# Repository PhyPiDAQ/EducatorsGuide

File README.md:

# PhyPiDAQ  Educators' Guide README

[Full Educators Tutorial in English](EducatorsGuide.md)

[Ausführliche Anleitung in deutscher Sprache](Anleitung.md)

## Summary  

The PhyPiDAQ project aims to provide students access to state-of-the-art measurement technology and data
acquisition tools. As it is based on standardized protocols and hardware, it can not only be cheaper to
set up than similar offers but also gives a great educational introduction in methods of modern science. 
Additionally, the measuring technology can be run off a power bank, making it portable and allowing great
experiments in nature. This project targets students from middle school up to undergraduates at the university
level with great matching educational concepts.
  
This is the general tutorial aming at educators. 
If you are looking for hardware guides, build instructions or software details, please check out our
other [repositories](https://github.com/PhyPiDAQ).

#### Currently available Documentation

 - [Software Description](https://github.com/PhyPiDAQ/PhyPiDAQ/tree/main/docs/Documentation_en.md)
 - [Educators Guide](https://github.com/PhyPiDAQ/EducatorsGuide/blob/main/EducatorsGuide.md)
 - [Hardware build instructions](https://github.com/PhyPiDAQ/MeasuringCase/blob/main/Documentation_en.md)

## Übersicht in Deutscher Sprache

Das PhyPiDAQ-Projekt zielt darauf ab, Studierenden und SchülerInnen Zugang zu modernster Messtechnik
und Datenerfassung zu geben. Da es auf offenen, standardisierten Protokollen und leicht verfügbarer
Hardware basiert, kann es nicht nur kostengünstig eingerichtet werden, sondern bietet auch eine 
hervorragende pädagogische Einführung in die Messmethoden der modernen Wissenschaft. Die Messtechnik 
kann mit einer Powerbank betrieben werden, was sie tragbar macht und Experimente auch in freier Natur
ermöglicht. *PhyPiDAQ* richtet sich an SchülerInnen von der Mittelstufe bis hin zu Studierenden auf Universitätsebene. 

Diese allgemeine Anleitung richtet sich an Lehrkräfte.
Wenn Sie nach Hardware-Beschreibungen, Bauanleitungen oder einer detaillierten Beschreibung der Software suchen, schauen Sie sich bitte unsere anderen
[Repositories](https://github.com/PhyPiDAQ) an.

#### Derzeit verfügbare Dokumentation

 - [Anleitung für Lehrkräfte](https://github.com/PhyPiDAQ/EducatorsGuide/blob/main/Anleitung.md)
 - [Einführungskurs für Schülerinnen und Schüler](https://github.com/PhyPiDAQ/EducatorsGuide/blob/main/docs/Kurs_digitale_Messwerterfassung_mit_PhyPiDAQ.pdf)
 - [Beschreibung der Software](https://github.com/PhyPiDAQ/PhyPiDAQ/blob/main/docs/Dokumentation_de.md)
 - [Bauanleitung Messkoffer](https://github.com/PhyPiDAQ/MeasuringCase/blob/main/Dokumentation_de.md)
 - [Leitfaden für das Experimentieren mit PhyPiDAQ](https://github.com/LangP14/EducatorsGuide/blob/main/Leitfaden%20fuer%20das%20Experimentieren%20mit%20PhyPiDAQ.md)

## Contributing

For information on how to contribute to this project, please refer to the [CONTRIBUTING.md](CONTRIBUTING.md) file.

## License

This project is licensed under the `MIT BSD 2-Clause License`. For more information refer to the [LICENSE](LICENSE) file.

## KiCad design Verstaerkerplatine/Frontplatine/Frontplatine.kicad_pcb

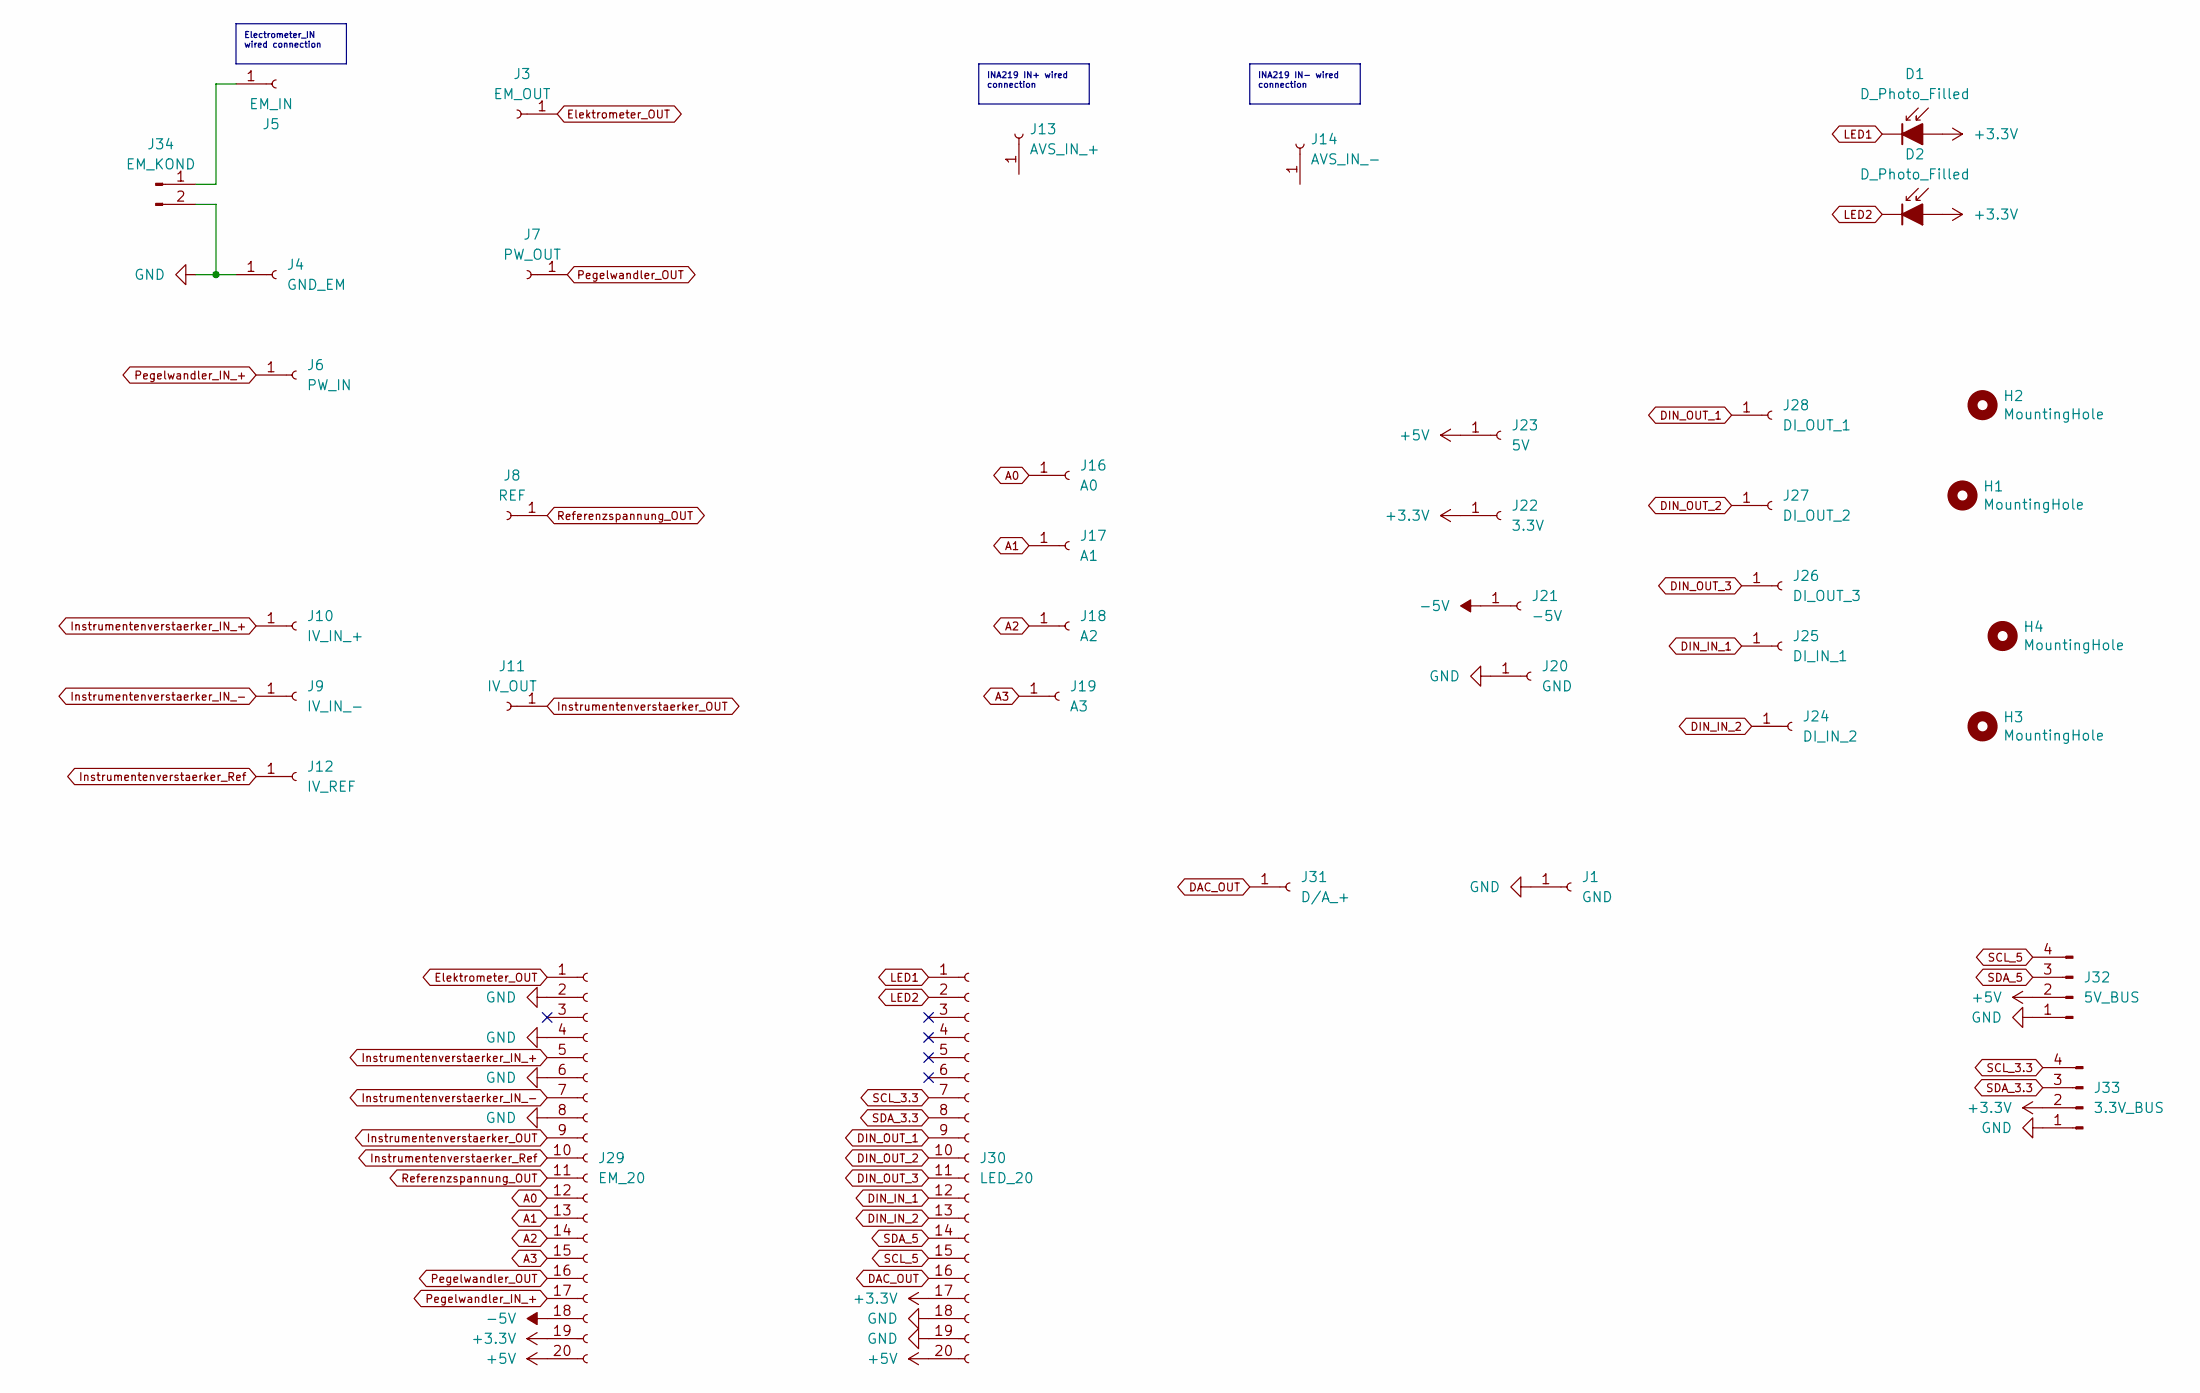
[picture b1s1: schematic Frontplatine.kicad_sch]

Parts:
D1, D2: D_Photo_Filled; LED_D5.0mm_FlatTop
H1, H2, H3, H4: MountingHole; MountingHole_3.2mm_M3
J1, J20: GND; MBU_1
J3: EM_OUT; MBU_1
J4: GND_EM; MBU_1
J5: EM_IN; MBU_1
J6: PW_IN; MBU_1
J7: PW_OUT; MBU_1
J8: REF; MBU_1
J9: IV_IN_-; MBU_1
J10: IV_IN_+; MBU_1
J11: IV_OUT; MBU_1
J12: IV_REF; MBU_1
J13: AVS_IN_+; MBU_1
J14: AVS_IN_-; MBU_1
J16: A0; MBU_1
J17: A1; MBU_1
J18: A2; MBU_1
J19: A3; MBU_1
J21: -5V; MBU_1
J22: 3.3V; MBU_1
J23: 5V; MBU_1
J24: DI_IN_2; MBU_1
J25: DI_IN_1; MBU_1
J26: DI_OUT_3; MBU_1
J27: DI_OUT_2; MBU_1
J28: DI_OUT_1; MBU_1
J29: EM_20; PinHeader_1x20_P2.54mm_Vertical_SMD_Pin1Left
J30: LED_20; PinHeader_1x20_P2.54mm_Vertical_SMD_Pin1Left
J31: D/A_+; MBU_1
J32: 5V_BUS; PinSocket_1x04_P2.00mm_Vertical
J33: 3.3V_BUS; PinSocket_1x04_P2.00mm_Vertical
J34: EM_KOND; PinSocket_1x02_P2.54mm_Vertical

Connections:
+3.3V: D1.2 (A), D2.2 (A), J22.1, J29.19, J30.17, J33.2
+5V: J23.1, J29.20, J30.20, J32.2
-5V: J21.1, J29.18
A0: J16.1, J29.12
A1: J17.1, J29.13
A2: J18.1, J29.14
A3: J19.1, J29.15
DAC_OUT: J30.16, J31.1
DIN_IN_1: J25.1, J30.12
DIN_IN_2: J24.1, J30.13
DIN_OUT_1: J28.1, J30.9
DIN_OUT_2: J27.1, J30.10
DIN_OUT_3: J26.1, J30.11
Elektrometer_OUT: J3.1, J29.1
GND: J1.1, J4.1, J20.1, J29.2, J29.4, J29.6, J29.8, J30.18, J30.19, J32.1, J33.1, J34.2
Instrumentenverstaerker_IN_+: J10.1, J29.5
Instrumentenverstaerker_IN_-: J9.1, J29.7
Instrumentenverstaerker_OUT: J11.1, J29.9
Instrumentenverstaerker_Ref: J12.1, J29.10
LED1: D1.1 (K), J30.1
LED2: D2.1 (K), J30.2
unnamed: J5.1, J34.1
Pegelwandler_IN_+: J6.1, J29.17
Pegelwandler_OUT: J7.1, J29.16
Referenzspannung_OUT: J8.1, J29.11
SCL_3.3: J30.7, J33.4
SCL_5: J30.15, J32.4
SDA_3.3: J30.8, J33.3
SDA_5: J30.14, J32.3

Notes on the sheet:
INA219 IN+ wired connection
Electrometer_IN wired connection
INA219 IN- wired connection

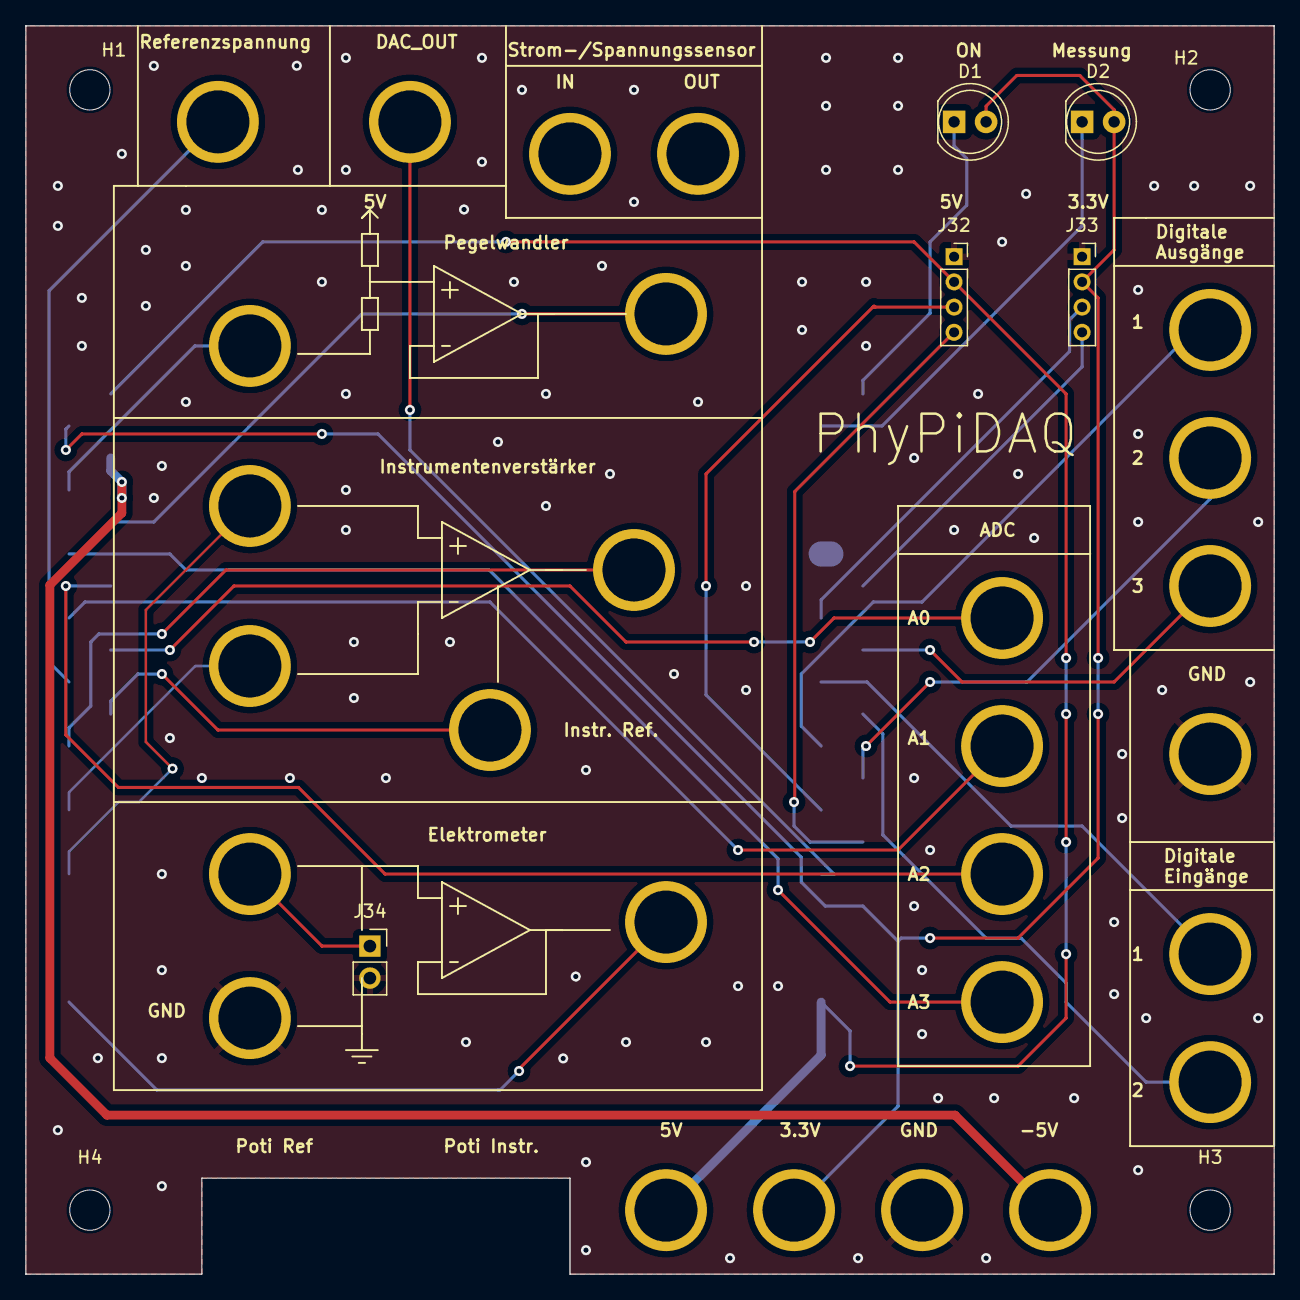
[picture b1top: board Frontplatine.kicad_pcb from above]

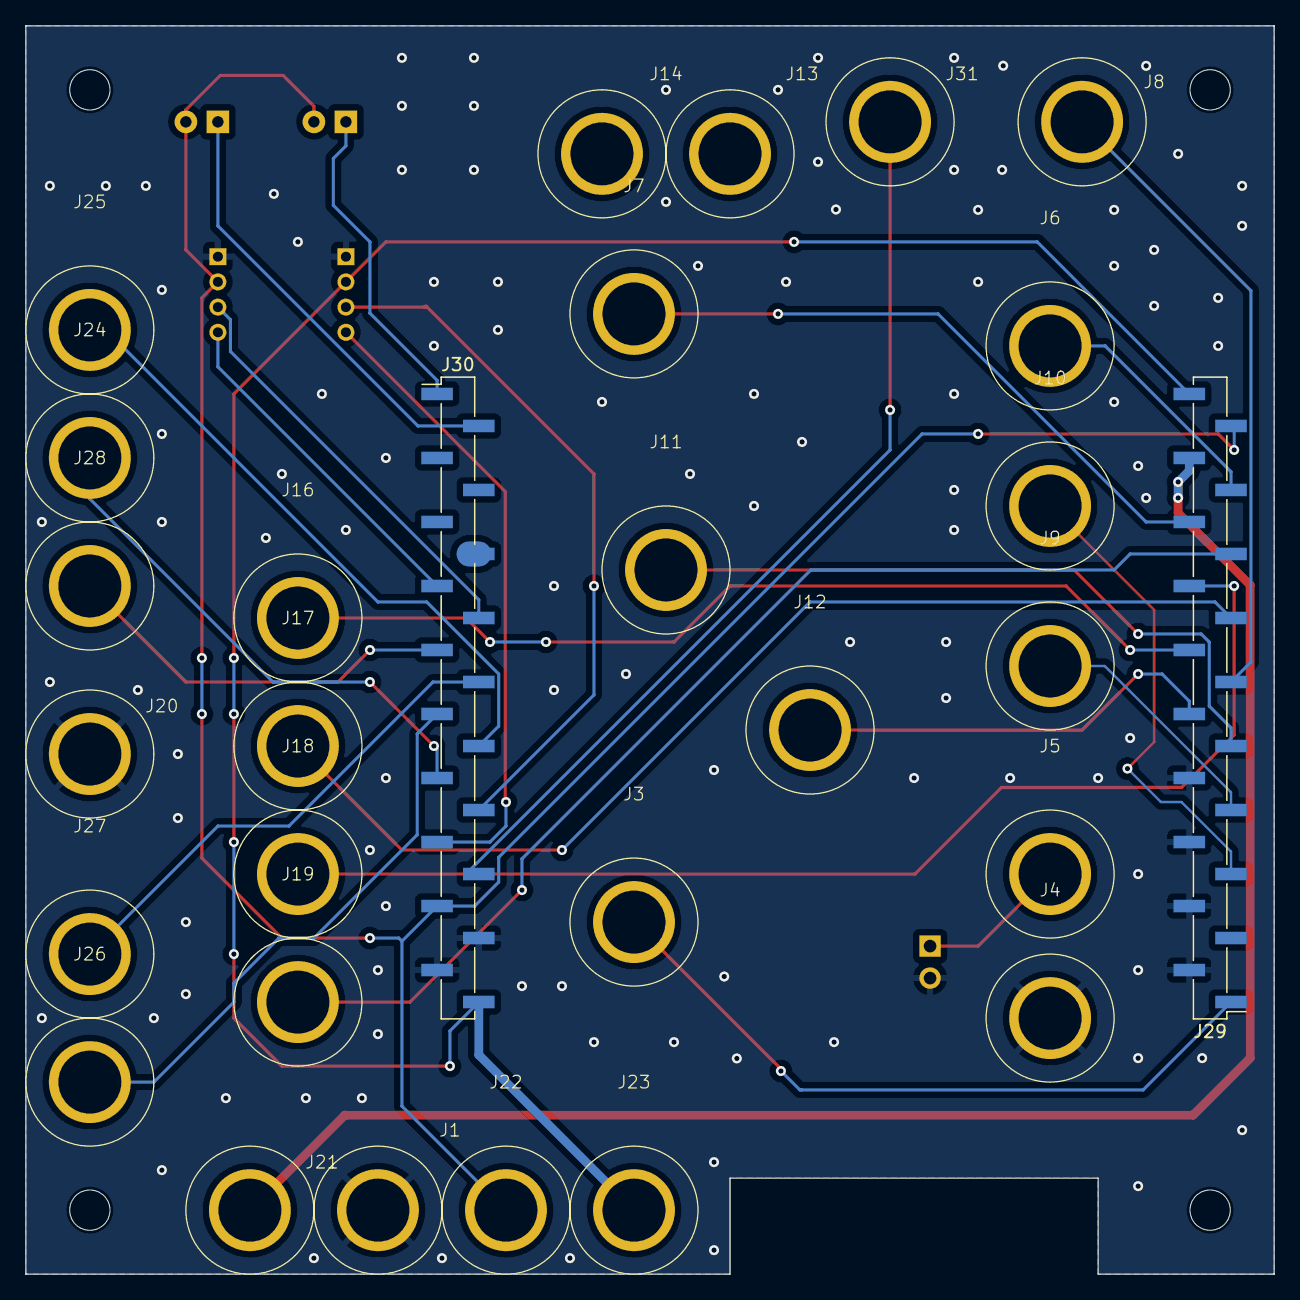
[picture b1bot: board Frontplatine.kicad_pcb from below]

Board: 2 copper layers, 99.1 x 99.1 mm, 38 parts (29 on the bottom side), 29 nets.

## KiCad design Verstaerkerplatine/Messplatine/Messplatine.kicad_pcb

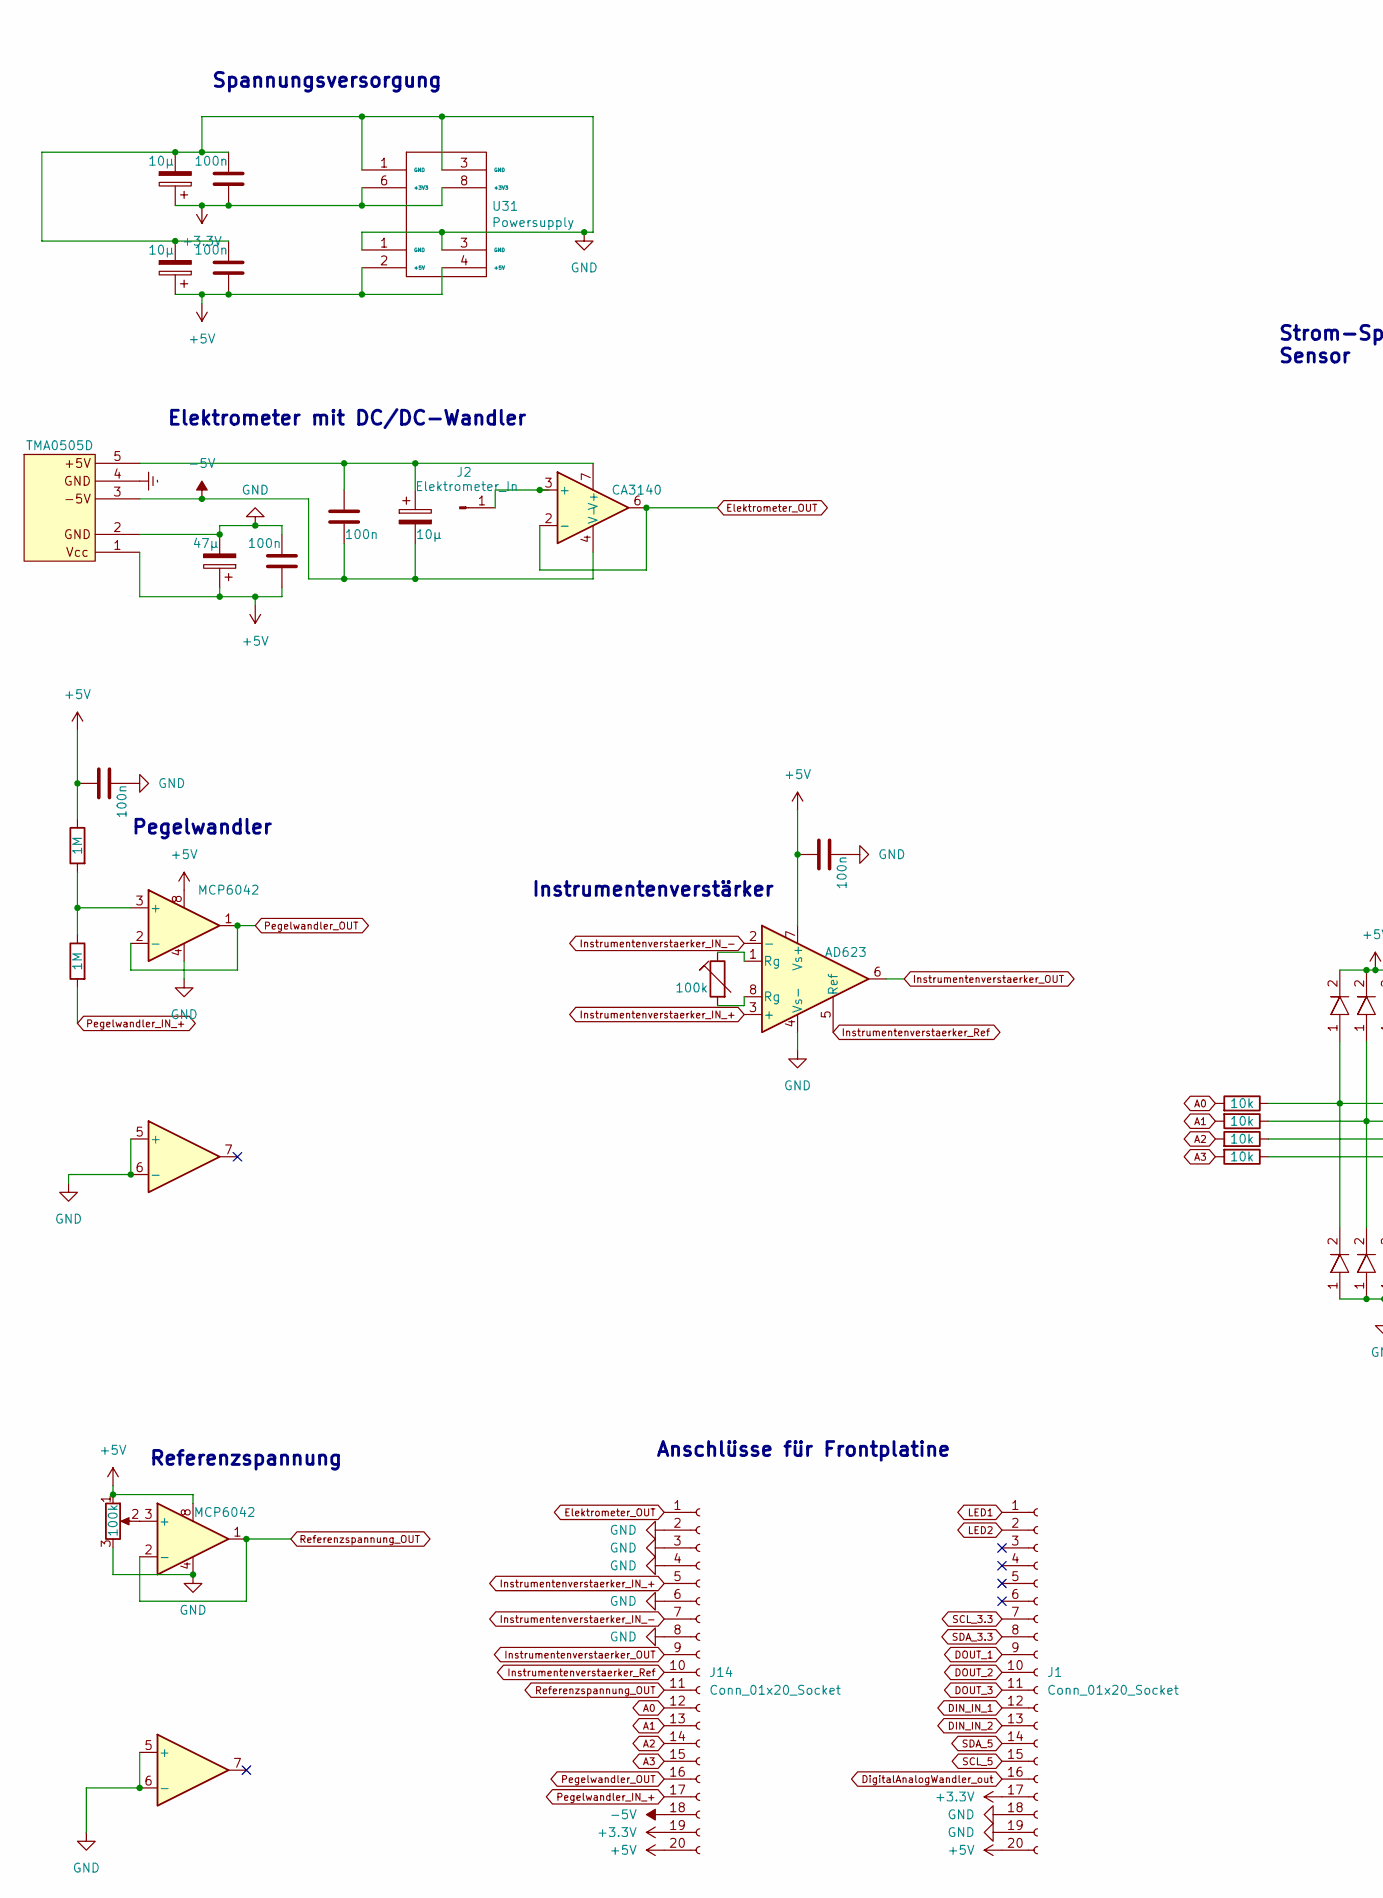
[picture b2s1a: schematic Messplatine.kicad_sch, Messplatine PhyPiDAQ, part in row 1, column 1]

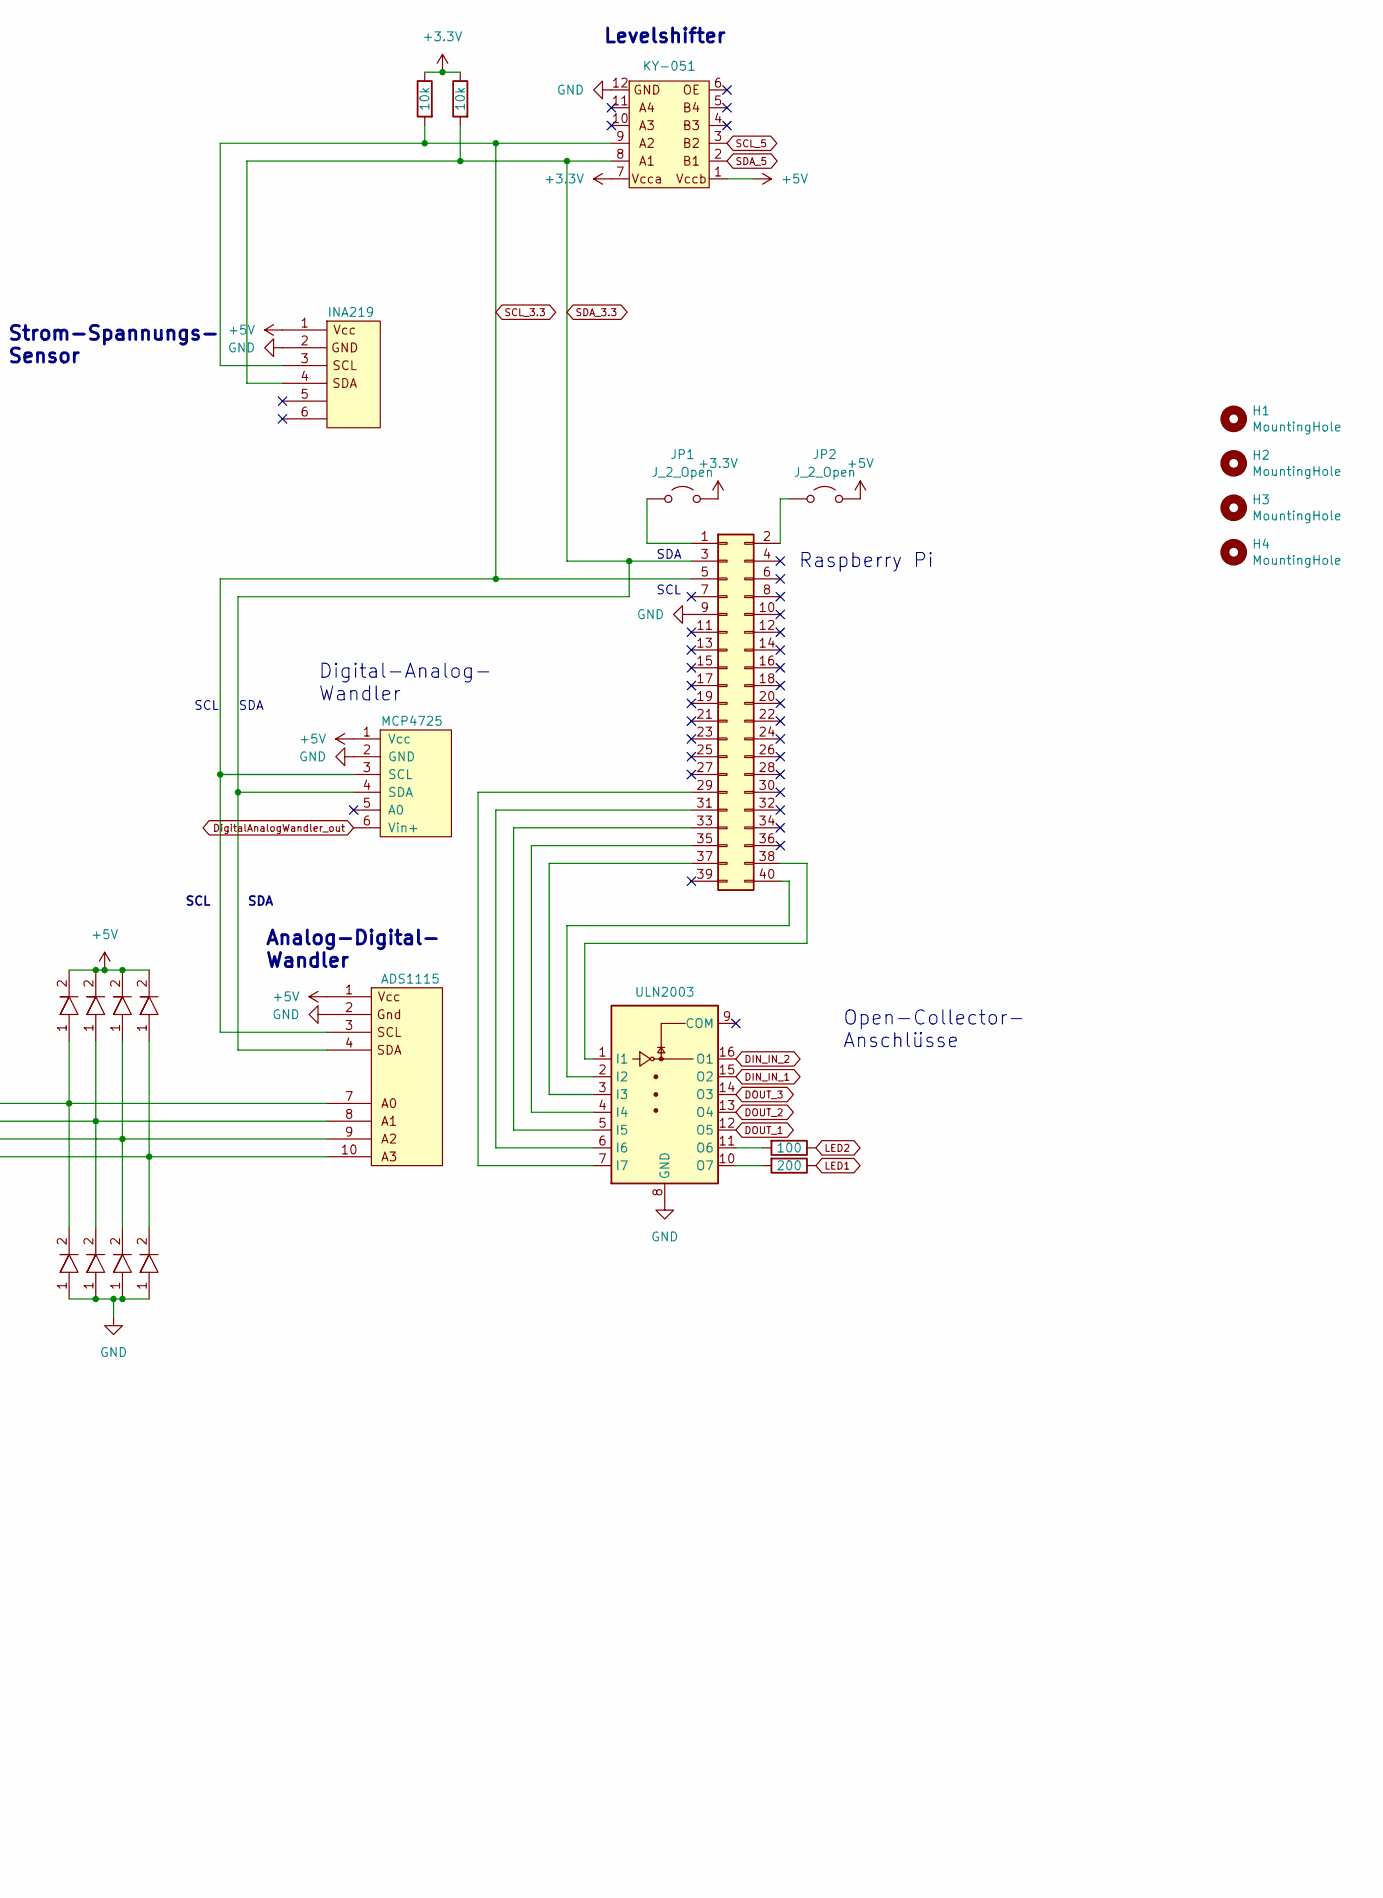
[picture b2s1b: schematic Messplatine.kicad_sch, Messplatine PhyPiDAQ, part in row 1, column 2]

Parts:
C1, C2, C7, C8, C9, C11: 100n; kerko
C3: 47µ; elko
C5, C6, C10: 10µ; elko
D1, D2, D3, D4, D5, D6, D7, D8: DIODE_small; Diode
H1, H2, H3, H4: MountingHole; MountingHole_3.2mm_M3
J1, J14: Conn_01x20_Socket; PinSocket_1x20_P2.54mm_Vertical
J2: Elektrometer_In; PinHeader_1x01_P2.54mm_Vertical
J26: Conn_02x20_Odd_Even; 40pin
JP1, JP2: J_2_Open; PinHeader_1x02_P2.54mm_Vertical
R1, R2: 1M; Resistor
R3: 100k; Poti
R4, R5, R6, R7, R8, R9: 10k; Resistor
R10: 100; Resistor
R11: 200; Resistor
RV1: 100k; Poti
U1, U7: MCP6042
U3: TMA0505D
U4: CA3140
U5: AD623
U6: INA219
U8: ADS1115
U9: MCP4725
U10: KY-051
U11: ULN2003
U31: Powersupply; powersupply

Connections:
+3.3V: C5.1, C7.1, J1.17, J14.19, JP1.2 (B), R8.1, R9.1, U10.7, U31.6 (+3V3), U31.8 (+3V3)
+5V: C1.1, C2.1, C3.1, C6.1, C8.1, C11.1, D1.2 (A), D3.2 (A), D5.2 (A), D7.2 (A), J1.20, J14.20, JP2.2 (B), R1.1, RV1.1, U1.8, U3.1, U5.7 (Vs+), U6.1, U7.8, U8.1, U9.1 (Vcc), U10.1, U31.2 (+5V), U31.4 (+5V)
-5V: C9.2, C10.2, J14.18, U3.3, U4.4 (V-)
A0: J14.12, R4.2
A1: J14.13, R5.2
A2: J14.14, R6.2
A3: J14.15, R7.2
DIN_IN_1: J1.12, U11.15 (O2)
DIN_IN_2: J1.13, U11.16 (O1)
DOUT_1: J1.9, U11.12 (O5)
DOUT_2: J1.10, U11.13 (O4)
DOUT_3: J1.11, U11.14 (O3)
DigitalAnalogWandler_out: J1.16, U9.6 (Vin+)
Elektrometer_OUT: J14.1, U4.2 (-), U4.6
GND: C1.2, C2.2, C3.2, C5.2, C6.2, C7.2, C8.2, C11.2, D2.1 (K), D4.1 (K), D6.1 (K), D8.1 (K), J1.18, J1.19, J14.2, J14.3, J14.4, J14.6, J14.8, J26.9, RV1.3, U1.4, U1.5 (+), U1.6 (-), U3.2, U5.4 (Vs-), U6.2, U7.4, U7.5 (+), U7.6 (-), U8.2, U9.2 (GND), U10.12, U11.8 (GND), U31.1 (GND), U31.3 (GND)
Instrumentenverstaerker_IN_+: J14.5, U5.3 (+)
Instrumentenverstaerker_IN_-: J14.7, U5.2 (-)
Instrumentenverstaerker_OUT: J14.9, U5.6
Instrumentenverstaerker_Ref: J14.10, U5.5 (Ref)
LED1: J1.1, R11.1
LED2: J1.2, R10.1
unnamed: D1.1 (K), D2.2 (A), R4.1, U8.7
unnamed: D3.1 (K), D4.2 (A), R5.1, U8.8
unnamed: D5.1 (K), D6.2 (A), R6.1, U8.9
unnamed: D7.1 (K), D8.2 (A), R7.1, U8.10
unnamed: J2.1, U4.3 (+)
unnamed: J26.1, JP1.1 (A)
unnamed: J26.2, JP2.1 (A)
unnamed: J26.29, U11.7 (I7)
unnamed: J26.31, U11.6 (I6)
unnamed: J26.33, U11.5 (I5)
unnamed: J26.35, U11.4 (I4)
unnamed: J26.37, U11.3 (I3)
unnamed: J26.38, U11.1 (I1)
unnamed: J26.40, U11.2 (I2)
unnamed: R1.2, R2.1, U1.3 (+)
unnamed: R3.1, U5.1 (Rg)
unnamed: R3.2, U5.8 (Rg)
unnamed: RV1.2, U7.3 (+)
unnamed: C9.1, C10.1, U3.5, U4.7 (V+)
unnamed: R10.2, U11.11 (O6)
unnamed: R11.2, U11.10 (O7)
Pegelwandler_IN_+: J14.17, R2.2
Pegelwandler_OUT: J14.16, U1.1, U1.2 (-)
Referenzspannung_OUT: J14.11, U7.1, U7.2 (-)
SCL_3.3: J1.7, J26.5, R9.2, U6.3, U8.3, U9.3 (SCL), U10.9
SCL_5: J1.15, U10.3
SDA_3.3: J1.8, J26.3, R8.2, U6.4, U8.4, U9.4 (SDA), U10.8
SDA_5: J1.14, U10.2

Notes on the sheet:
Raspberry Pi
Anschlüsse für Frontplatine
Instrumentenverstärker
SDA
SCL
Strom-Spannungs- Sensor
Referenzspannung
Levelshifter
Analog-Digital- Wandler
Pegelwandler
Elektrometer mit DC/DC-Wandler
Open-Collector- Anschlüsse
Digital-Analog- Wandler
Spannungsversorgung

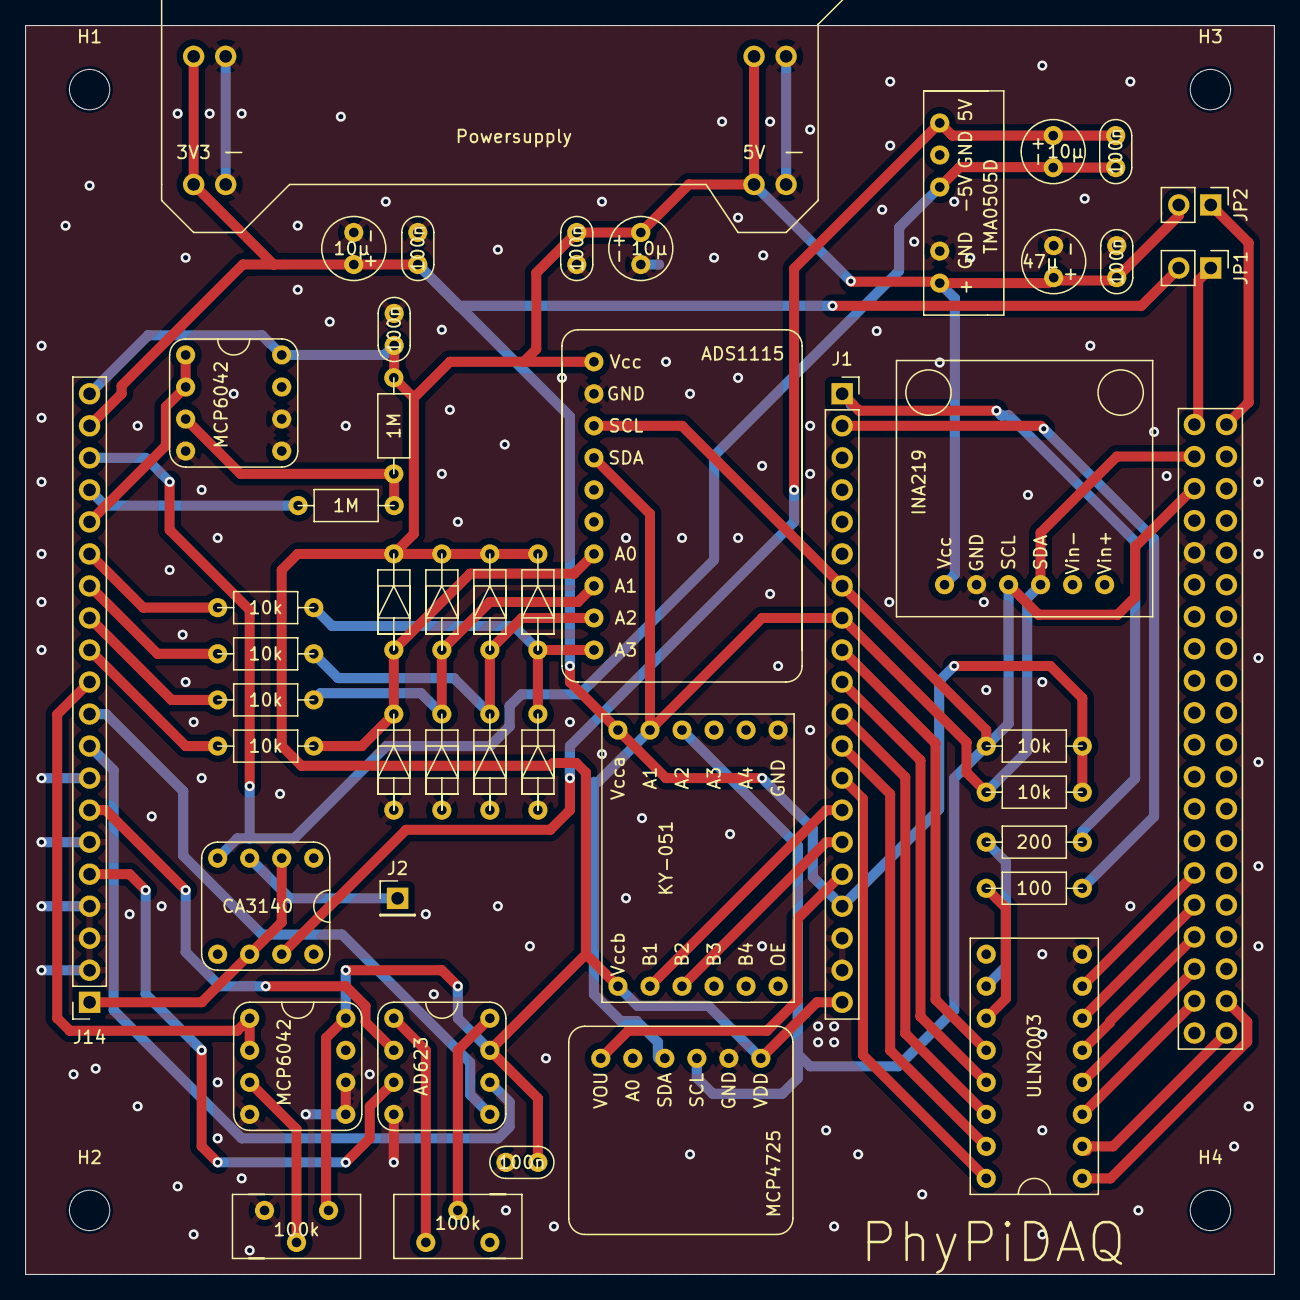
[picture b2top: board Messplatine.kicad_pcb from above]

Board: 2 copper layers, 99.1 x 99.1 mm, 51 parts (0 on the bottom side), 49 nets.

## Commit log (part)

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2022-02-07 Add GitHub Actions
2022-02-07 Fix markdown
2022-02-10 Sync content
2022-02-10 Fix wrong description
2022-02-10 Spelling fix
2022-02-12 initial version of Educators Guide
2022-02-12 completed README
2022-02-12 added (revised) stutents course by M. Aupperle and included in documentation files
2022-02-12 revised version Einrichten des RPiO
2022-02-13 fixed merging problems
2022-02-13 more additions and corrections to EditorsGuide and Anleitung
2022-02-15 restricted line length to 120
2022-02-19 added links to all documentations
2022-02-19 restuctured: experiments in ./Experimente and ./experiments
2022-02-20 proper formatting of images
2022-02-24 fix formatting of header
2022-02-27 Schaltpläne in Erklärungen der Experimente
2022-02-27 added schematics of instrumentaion amplifier
2022-02-27 added schematic overview
2022-03-01 added english version capacitor experiment
2022-03-02 new experiments taken from German examples
2022-03-03 included link to new introductory material
2022-03-05 adjusted resolution
2022-03-05 added non-liner temperature sensor
2022-03-06 added Author
2022-03-19 added references
2022-03-21 added reference to English web page
2022-03-21 fixed formatting of references
2022-11-03 fixed broken Links to Documentation
2022-11-03 fixed link
2023-05-22 fixes for latest version >=1.2.2
2023-05-22 fixed address of download link
2023-05-29 fixed format in table with linux commands
2023-06-27 remove self-referencing link
2023-06-27 added markdown version of introductory course
2023-07-09 fixted internal and external links
2023-08-08 Update README.md
    Änderung eines toten Links und Verbesserung von Rechtschreibfehlern.
2023-08-19 added description of gamma ray experiments with Radiacode 102
2023-08-19 added config files
2023-08-19 added headings and physics background, decay of Ra-induced activity on baloon
2023-09-09 english name and some improvements
2023-09-09 replaced decay curve (now using RC102)
2023-09-09 better differential spectrum
2023-09-11 first round of corrections done
2023-09-17 reformatted source code
2023-09-17 added hint to show-spectrum.py in the radiacode library
2023-10-18 First Upload of the "Leitfaden" in German
2023-10-25 First Version
2023-10-25 Pictures for the document "Leitfaden"
2023-10-25 First Upload
2023-10-25 New images because of the document "ideales Gasgesetz"
    -1-
2023-10-25 New images because of the document "ideales Gasgesetz"
    -2-
2023-10-25 First Upload "ideales Gasgesetz"
2023-10-25 Update README.md
    Add Information about the new documentation "Leitfaden"
2023-10-28 added bibliographic links to relevant Master Theses
2024-07-18 correction in description
2024-08-02 initial, still incomplete version
2024-08-02 added images
2024-08-03 more complete description of software
2024-08-03 added hint for sound card system settings
2024-08-05 minor improvements
2024-08-09 initial German version
2024-08-09 more on data analysis
2024-08-09 manual improvements to DeeepL translatoin
2024-08-13 minor language improvements
2024-08-13 resolved merge conflict
2024-08-13 more small fixes
2024-08-13 included 1st results
2024-08-13 minor mods
2024-08-13 remuved backup
2024-08-13 remuved duplicate
2024-08-13 improved formatting
2024-08-14 added results from German version
2024-08-18 small language fixes
2024-08-20 included DIY Particle Detector
2024-08-25 hints for installation
2024-08-27 description of simple installation
2024-08-29 added installation hints
2024-08-31 commented inverted pule on image
2024-08-31 commented inverted pulse
2024-08-31 added rough calibration information
2024-09-05 included measurement of environmental radioactivity
2024-09-06 environmental radioactivity as first example
2024-09-10 improved docu and added pulse height analysis
2024-09-10 better histogram title
2024-09-11 updated csv data
2024-09-11 spell checking
2024-09-11 new fiure
2024-09-12 more spelling fixes
2024-09-12 included pulse height analysis
2024-09-13 pulse heights for environmenal radioactivity as log-plot
2024-09-13 pulse height analyis with ambient radiation
2024-09-14 added analysis code and data
2024-09-14 added latest corrections
2024-09-14 english figure lables & ruff formatting
2024-09-15 fixed typo in header
2024-09-15 show non-inverted pulse as example
2024-09-15 smaller bin size
2024-09-16 ruff formatting
2024-09-22 fixed some typoes
2024-09-24 hint why the shielded electon detector is a gamma detector
2024-10-05 unbreakable thin space for units
2024-10-19 improved formatting of source code
2024-11-30 DIY-Teilchendetektor: Dokumentation zur Speicherung der Eigenschaften der Wellenformen
2024-11-30 documented format of stored wave form features
2024-12-01 added spectra of pulses classified with pulse shapes
2025-02-15 added Radon measurement
2025-02-15 improved section on Radon
2025-02-16 fixed conflict
2025-02-16 fixed formatting
2025-03-01 LaTeX strings as raw
2025-05-07 added kicad files
2025-05-07 added front circuti board
2025-05-07 added missing image
2025-05-08 improved docu
2025-05-10 LED connection moved
2025-05-11 added Jumpers for 3.3V and 5V from Raspberry Pi
2025-05-11 fixed docu
2025-05-12 plots of latest version
2025-05-13 introduced direct wire connections for CA3160 and INA219
2025-05-13 wired connection for CA3140 in and IN219 IN+ and IN-
2025-07-09 fixed typo
2025-12-05 small fixes
2025-12-05 included RC-110
2026-01-08 updated for latest RadiaCode devices
